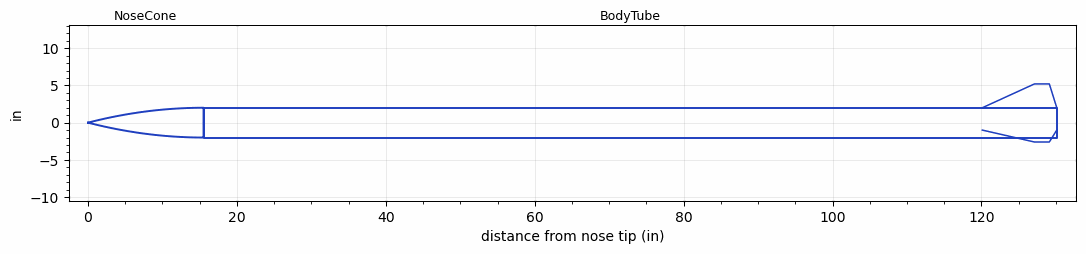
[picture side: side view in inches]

<RASAeroDocument>
 <FileVersion>2</FileVersion>
 <RocketDesign>
  <NoseCone>
   <Length>15.516</Length>
   <Diameter>4</Diameter>
   <Shape>Parabolic</Shape>
   <BluntRadius>0.1</BluntRadius>
   <Location>0</Location>
  </NoseCone>
  <BodyTube>
   <Length>114.6</Length>
   <Diameter>4</Diameter>
   <LaunchShoeArea>0.09</LaunchShoeArea>
   <Location>15.516</Location>
   <Fin>
    <Count>3</Count>
    <Chord>10</Chord>
    <Span>3.2</Span>
    <SweepDistance>7</SweepDistance>
    <TipChord>2</TipChord>
    <Thickness>0.25</Thickness>
    <LERadius>0.125</LERadius>
    <Location>10</Location>
    <AirfoilSection>Double Wedge</AirfoilSection>
    <FX1>1</FX1>
   </Fin>
  </BodyTube>
  <Surface>Galvanized Metal</Surface>
  <ModifiedBarrowman>True</ModifiedBarrowman>
  <Turbulence>False</Turbulence>
  <UseBooster1>False</UseBooster1>
  <UseBooster2>False</UseBooster2>
 </RocketDesign>
 <LaunchSite>
  <Altitude>600</Altitude>
  <Pressure>0</Pressure>
  <RodAngle>1.2</RodAngle>
  <RodLength>20</RodLength>
  <Temperature>87</Temperature>
  <WindSpeed>10</WindSpeed>
 </LaunchSite>
 <Recovery>
  <Altitude1>1000</Altitude1>
  <Altitude2>1500</Altitude2>
  <DeviceType1>Parachute</DeviceType1>
  <DeviceType2>Parachute</DeviceType2>
  <Event1>True</Event1>
  <Event2>True</Event2>
  <Size1>30.57</Size1>
  <Size2>96</Size2>
  <EventType1>Apogee</EventType1>
  <EventType2>Altitude</EventType2>
  <CD1>0.75</CD1>
  <CD2>2.2</CD2>
 </Recovery>
 <SimulationList>
  <Simulation>
   <SustainerEngine>M2500T  (AT)</SustainerEngine>
   <SustainerLaunchWt>46.4</SustainerLaunchWt>
   <SustainerNozzleDiameter>2</SustainerNozzleDiameter>
   <SustainerCG>70.8</SustainerCG>
   <SustainerIgnitionDelay>0</SustainerIgnitionDelay>
   <Booster1SeparationDelay>0</Booster1SeparationDelay>
   <Booster1IgnitionDelay>0</Booster1IgnitionDelay>
   <IncludeBooster1>False</IncludeBooster1>
   <Booster2Delay>0</Booster2Delay>
   <IncludeBooster2>False</IncludeBooster2>
   <TimetoApogee>31.01061</TimetoApogee>
   <MaxAltitude>17353.39</MaxAltitude>
   <MaxVelocity>1411.031</MaxVelocity>
  </Simulation>
  <Simulation>
   <SustainerEngine>M2500T  (AT)</SustainerEngine>
   <SustainerLaunchWt>50.4</SustainerLaunchWt>
   <SustainerNozzleDiameter>2</SustainerNozzleDiameter>
   <SustainerCG>72</SustainerCG>
   <SustainerIgnitionDelay>0</SustainerIgnitionDelay>
   <Booster1SeparationDelay>0</Booster1SeparationDelay>
   <Booster1IgnitionDelay>0</Booster1IgnitionDelay>
   <IncludeBooster1>False</IncludeBooster1>
   <Booster2Delay>0</Booster2Delay>
   <IncludeBooster2>False</IncludeBooster2>
   <TimetoApogee>30.5906</TimetoApogee>
   <MaxAltitude>16344.66</MaxAltitude>
   <MaxVelocity>1294.998</MaxVelocity>
  </Simulation>
  <Simulation>
   <SustainerEngine>N2900-CL  (CTI)</SustainerEngine>
   <SustainerLaunchWt>74.8</SustainerLaunchWt>
   <SustainerNozzleDiameter>2</SustainerNozzleDiameter>
   <SustainerCG>74.5</SustainerCG>
   <SustainerIgnitionDelay>0</SustainerIgnitionDelay>
   <Booster1SeparationDelay>0</Booster1SeparationDelay>
   <Booster1IgnitionDelay>0</Booster1IgnitionDelay>
   <IncludeBooster1>False</IncludeBooster1>
   <Booster2Delay>0</Booster2Delay>
   <IncludeBooster2>False</IncludeBooster2>
   <TimetoApogee>42.83882</TimetoApogee>
   <MaxAltitude>30388.57</MaxAltitude>
   <MaxVelocity>1647.571</MaxVelocity>
  </Simulation>
  <Simulation>
   <SustainerEngine>L1500T  (AT)</SustainerEngine>
   <SustainerLaunchWt>42.5</SustainerLaunchWt>
   <SustainerNozzleDiameter>1</SustainerNozzleDiameter>
   <SustainerCG>62</SustainerCG>
   <SustainerIgnitionDelay>0</SustainerIgnitionDelay>
   <Booster1SeparationDelay>0</Booster1SeparationDelay>
   <Booster1IgnitionDelay>0</Booster1IgnitionDelay>
   <IncludeBooster1>False</IncludeBooster1>
   <Booster2Delay>0</Booster2Delay>
   <IncludeBooster2>False</IncludeBooster2>
   <TimetoApogee>23.42044</TimetoApogee>
   <MaxAltitude>8421.792</MaxAltitude>
   <MaxVelocity>779.4959</MaxVelocity>
  </Simulation>
  <Simulation>
   <SustainerEngine>M2500T  (AT)</SustainerEngine>
   <SustainerLaunchWt>47.7</SustainerLaunchWt>
   <SustainerNozzleDiameter>2</SustainerNozzleDiameter>
   <SustainerCG>68</SustainerCG>
   <SustainerIgnitionDelay>0</SustainerIgnitionDelay>
   <Booster1SeparationDelay>0</Booster1SeparationDelay>
   <Booster1IgnitionDelay>0</Booster1IgnitionDelay>
   <IncludeBooster1>False</IncludeBooster1>
   <Booster2Delay>0</Booster2Delay>
   <IncludeBooster2>False</IncludeBooster2>
   <TimetoApogee>30.93061</TimetoApogee>
   <MaxAltitude>17061.28</MaxAltitude>
   <MaxVelocity>1371.025</MaxVelocity>
  </Simulation>
 </SimulationList>
</RASAeroDocument>
